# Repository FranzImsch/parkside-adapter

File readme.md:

## Overview

Lidl sells batteries for their Parkside-branded power tools. These are 5S lithium-ion batteries that are well-constructed and cost approximately €20 for the 4 Ah version. While the cells are not from premium brands, they appear to be of relatively high quality. For instance, the 4 Ah battery I purchased contains Sunpower INR19/66 cells. Detailed information about these cells can be found here:  
[Parkside INR18650E 2000mAh (Blue) Review](https://lygte-info.dk/review/batteries2012/Parkside%20INR18650E%202000mAh%20(Blue)%20UK.html)  
[Sunpower High-Rate Lithium-Ion Battery Specifications](https://www.sunpowernewenergy.com/product/18650-high-rate-lithium-ion-battery-20p/)

Currently, Lidl offers a USB charger add-on for these batteries, but it has significant limitations. Its output power is restricted to 15 W, and it does not support charging the battery via USB.  
[Product page](https://www.lidl.de/p/parkside-20-v-akku-ladeadapter-pwca-20-li-a1/p100363956)

The adaptor described here comprises a 3D-printed enclosure and a PCB with soldered contacts that connect to the battery terminals. The interface PCB includes two mounting locations for power modules.

The screenshot shows a cross section view of the assembly.

The bi-directional 100 W USB-C module, based on the IP2368 chip, is used in the current implementation.

Future developments are planned, including a 240 W power module and a PCB with a microcontroller and control logic.

## IP2368

The IP2368 chip is available in several firmware versions. I chose the IP2368_I2C_NACT variant, which supports I2C communication and can function as a USB-C source immediately upon connection to a battery, without requiring an initial connection to a charger. Sourcing this chip outside China is challenging; I obtained mine via [LCSC](https://www.lcsc.com/product-detail/Power-Management-Specialized_INJOINIC-IP2368_I2C_COUT_C5372184.html). Note that a quotation request is necessary, as this chip is typically not in stock.

## Tasks

- [ ] Create and expand documentation (better photos)
- [ ] Replace the overview photo  
- [ ] Design a PCB for the microcontroller  
- [ ] Test the 100 W power module

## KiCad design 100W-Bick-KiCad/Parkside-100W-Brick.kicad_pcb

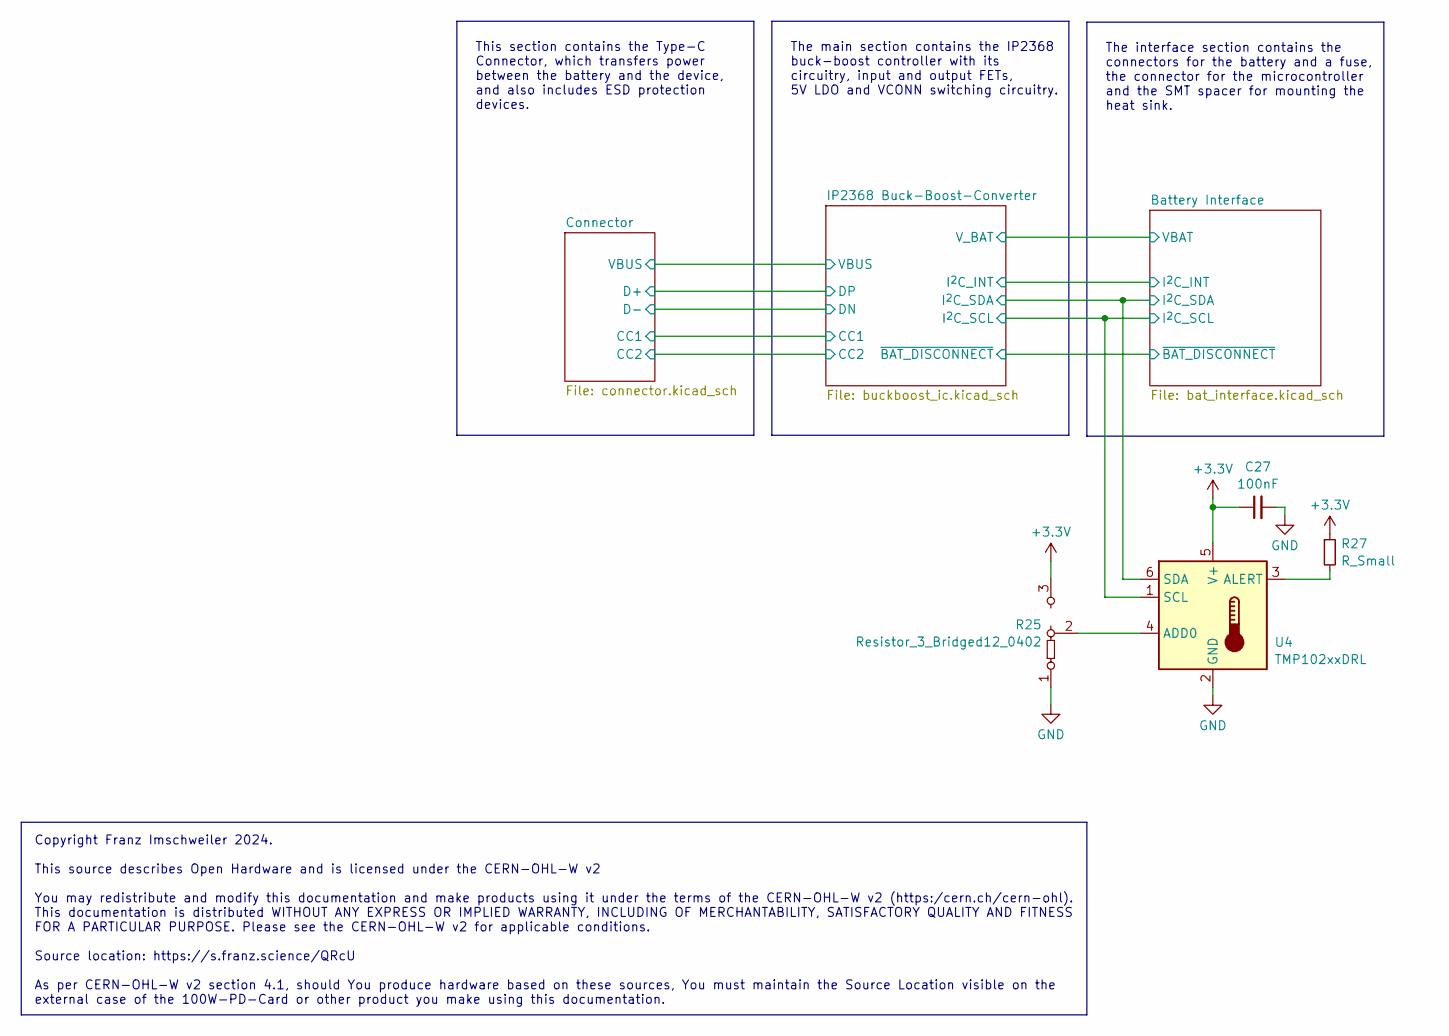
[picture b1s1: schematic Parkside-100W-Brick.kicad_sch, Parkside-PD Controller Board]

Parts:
C27: 100nF; C_0402_1005Metric_NoSilk
R25: Resistor_3_Bridged12_0402; R_0402_JUMPER3_NoSilk
R27: R_Small; R_0402_1005Metric_NoSilk
U4: TMP102xxDRL; SOT-563_NoSilk

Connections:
+3.3V: C27.1, R25.3 (B), R27.1, U4.5 (V+); also elsewhere on the board
/Battery Interface/I^{2}C_SCL: U4.1 (SCL); also elsewhere on the board
/Battery Interface/I^{2}C_SDA: U4.6 (SDA); also elsewhere on the board
GND: C27.2, R25.1 (A), U4.2 (GND); also elsewhere on the board
unnamed: R25.2 (C), U4.4 (ADD0)
unnamed: R27.2, U4.3 (ALERT)

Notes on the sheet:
The interface section contains the connectors for the battery and a fuse, the connector for the microcontroller and the SMT spacer for mounting the heat sink.
Copyright Franz Imschweiler 2024. This source describes Open Hardware and is licensed under the CERN-OHL-W v2 You may redistribute and modify this documentation and make products using it under the terms of the CERN-OHL-W v2 (https:/cern.ch/cern-ohl). This documentation is distributed WITHOUT ANY E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
This section contains the Type-C Connector, which transfers power between the battery and the device, and also includes ESD protection devices.
The main section contains the IP2368 buck-boost controller with its circuitry, input and output FETs, 5V LDO and VCONN switching circuitry.

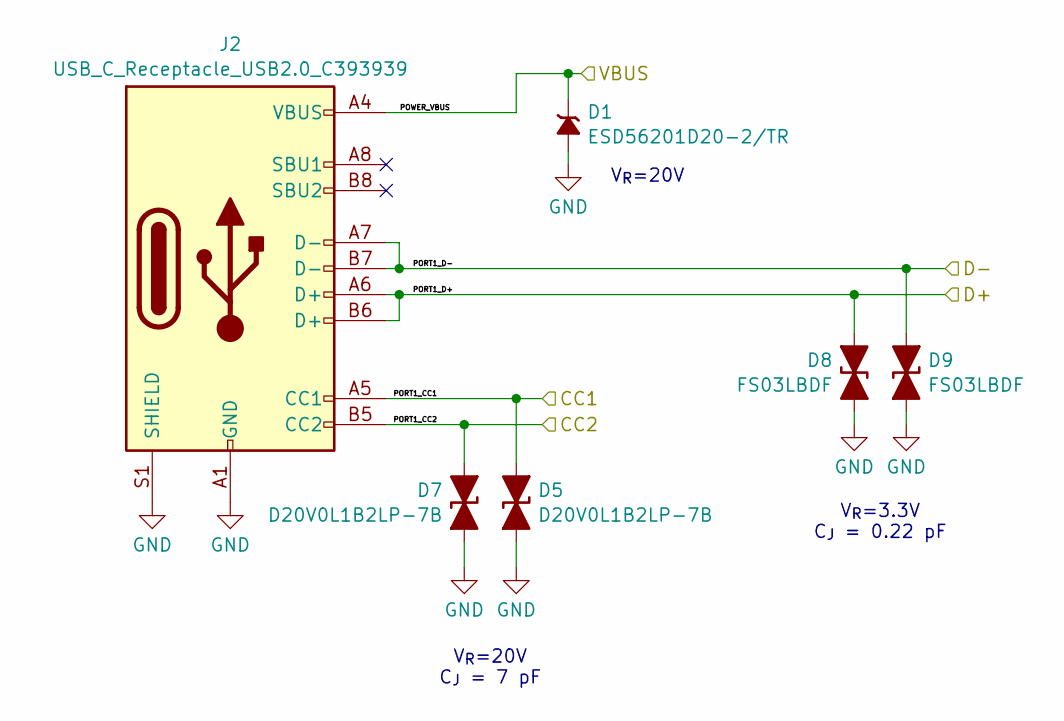
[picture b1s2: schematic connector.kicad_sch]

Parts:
D1: ESD56201D20-2/TR; ST_QFN1610_1_NoSilk
D5, D7: D20V0L1B2LP-7B; X1-DFN1006-2_P6X1_DIO
D8, D9: FS03LBDF; X1-DFN1006-2_P6X1_DIO
J2: USB_C_Receptacle_USB2.0_C393939; USB_C_Receptacle_C313131_TYPE-C-31-M-12

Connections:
/Connector/PORT1_CC1: D5.1 (A1), J2.A5 (CC1); also elsewhere on the board
/Connector/PORT1_CC2: D7.1 (A1), J2.B5 (CC2); also elsewhere on the board
/Connector/PORT1_D+: D8.1 (A1), J2.A6 (D+), J2.B6 (D+); also elsewhere on the board
/Connector/PORT1_D-: D9.1 (A1), J2.A7 (D-), J2.B7 (D-); also elsewhere on the board
/Connector/POWER_VBUS: D1.1 (K), J2.A4 (VBUS), J2.A9 (VBUS), J2.B4 (VBUS), J2.B9 (VBUS); also elsewhere on the board
GND: D1.2 (A), D5.2 (A2), D7.2 (A2), D8.2 (A2), D9.2 (A2), J2.A1 (GND), J2.A12 (GND), J2.B1 (GND), J2.B12 (GND), J2.S1 (SHIELD); also elsewhere on the board

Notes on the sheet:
V_{R}=20V C_{J} = 7 pF
V_{R}=20V
V_{R}=3.3V C_{J} = 0.22 pF

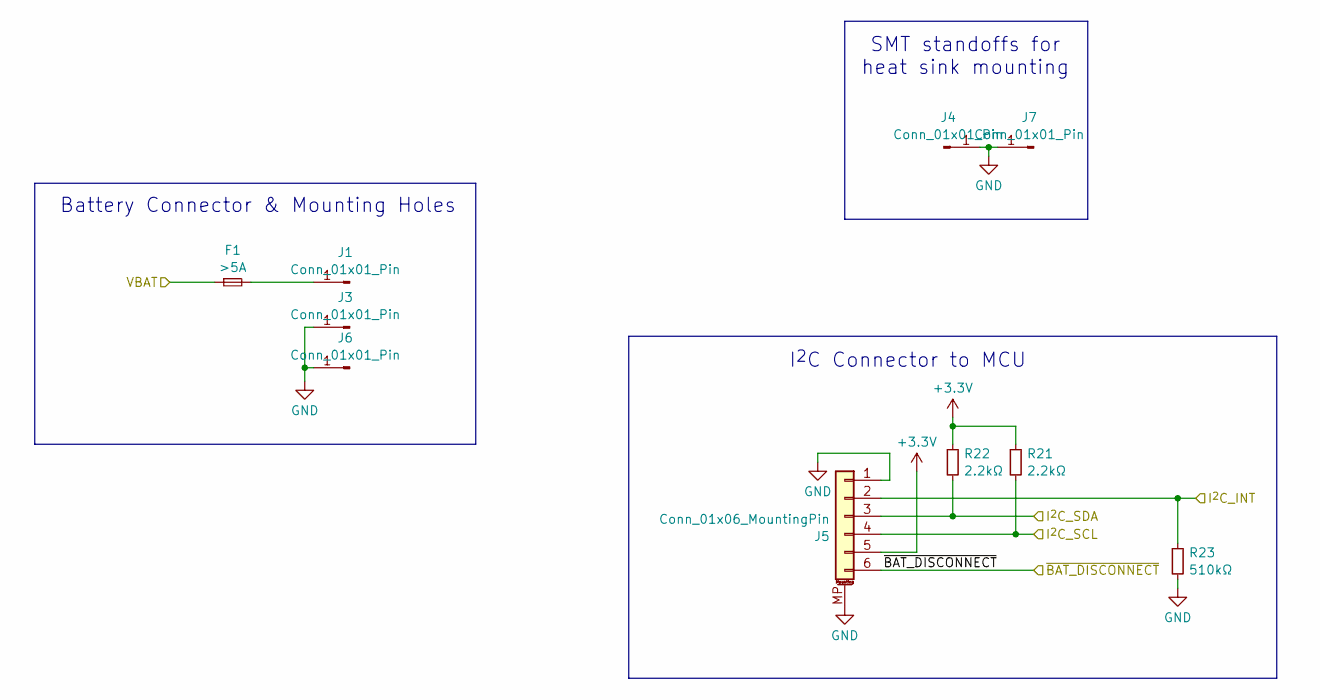
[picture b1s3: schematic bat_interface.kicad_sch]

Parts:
F1: >5A; Fuse_1206_3216Metric_NoSilk
J1, J3, J6: Conn_01x01_Pin; MountingHole_2.2mm_M2_Pad_Via_NoSilk
J4, J7: Conn_01x01_Pin; Mounting_Wuerth_WA-SMSI-M2_H6mm_9774060243
J5: Conn_01x06_MountingPin; JST_SH_SM06B-SRSS-TB_1x06-1MP_P1.00mm_Horizontal_NoSilk
R21, R22: 2.2kΩ; R_0402_1005Metric_NoSilk
R23: 510kΩ; R_0402_1005Metric_NoSilk

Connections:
+3.3V: J5.5, R21.1, R22.1; also elsewhere on the board
/Battery Interface/I^{2}C_INT: J5.2, R23.1; also elsewhere on the board
/Battery Interface/I^{2}C_SCL: J5.4, R21.2; also elsewhere on the board
/Battery Interface/I^{2}C_SDA: J5.3, R22.2; also elsewhere on the board
/Battery Interface/VBAT: F1.1; also elsewhere on the board
/Battery Interface/~BAT_DISCONNECT: J5.6; also elsewhere on the board
GND: J3.1, J4.1, J5.1, J5.MP (MountPin), J6.1, J7.1, R23.2; also elsewhere on the board
unnamed: F1.2, J1.1

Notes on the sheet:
Battery Connector & Mounting Holes
SMT standoffs for heat sink mounting
I^{2}C Connector to MCU

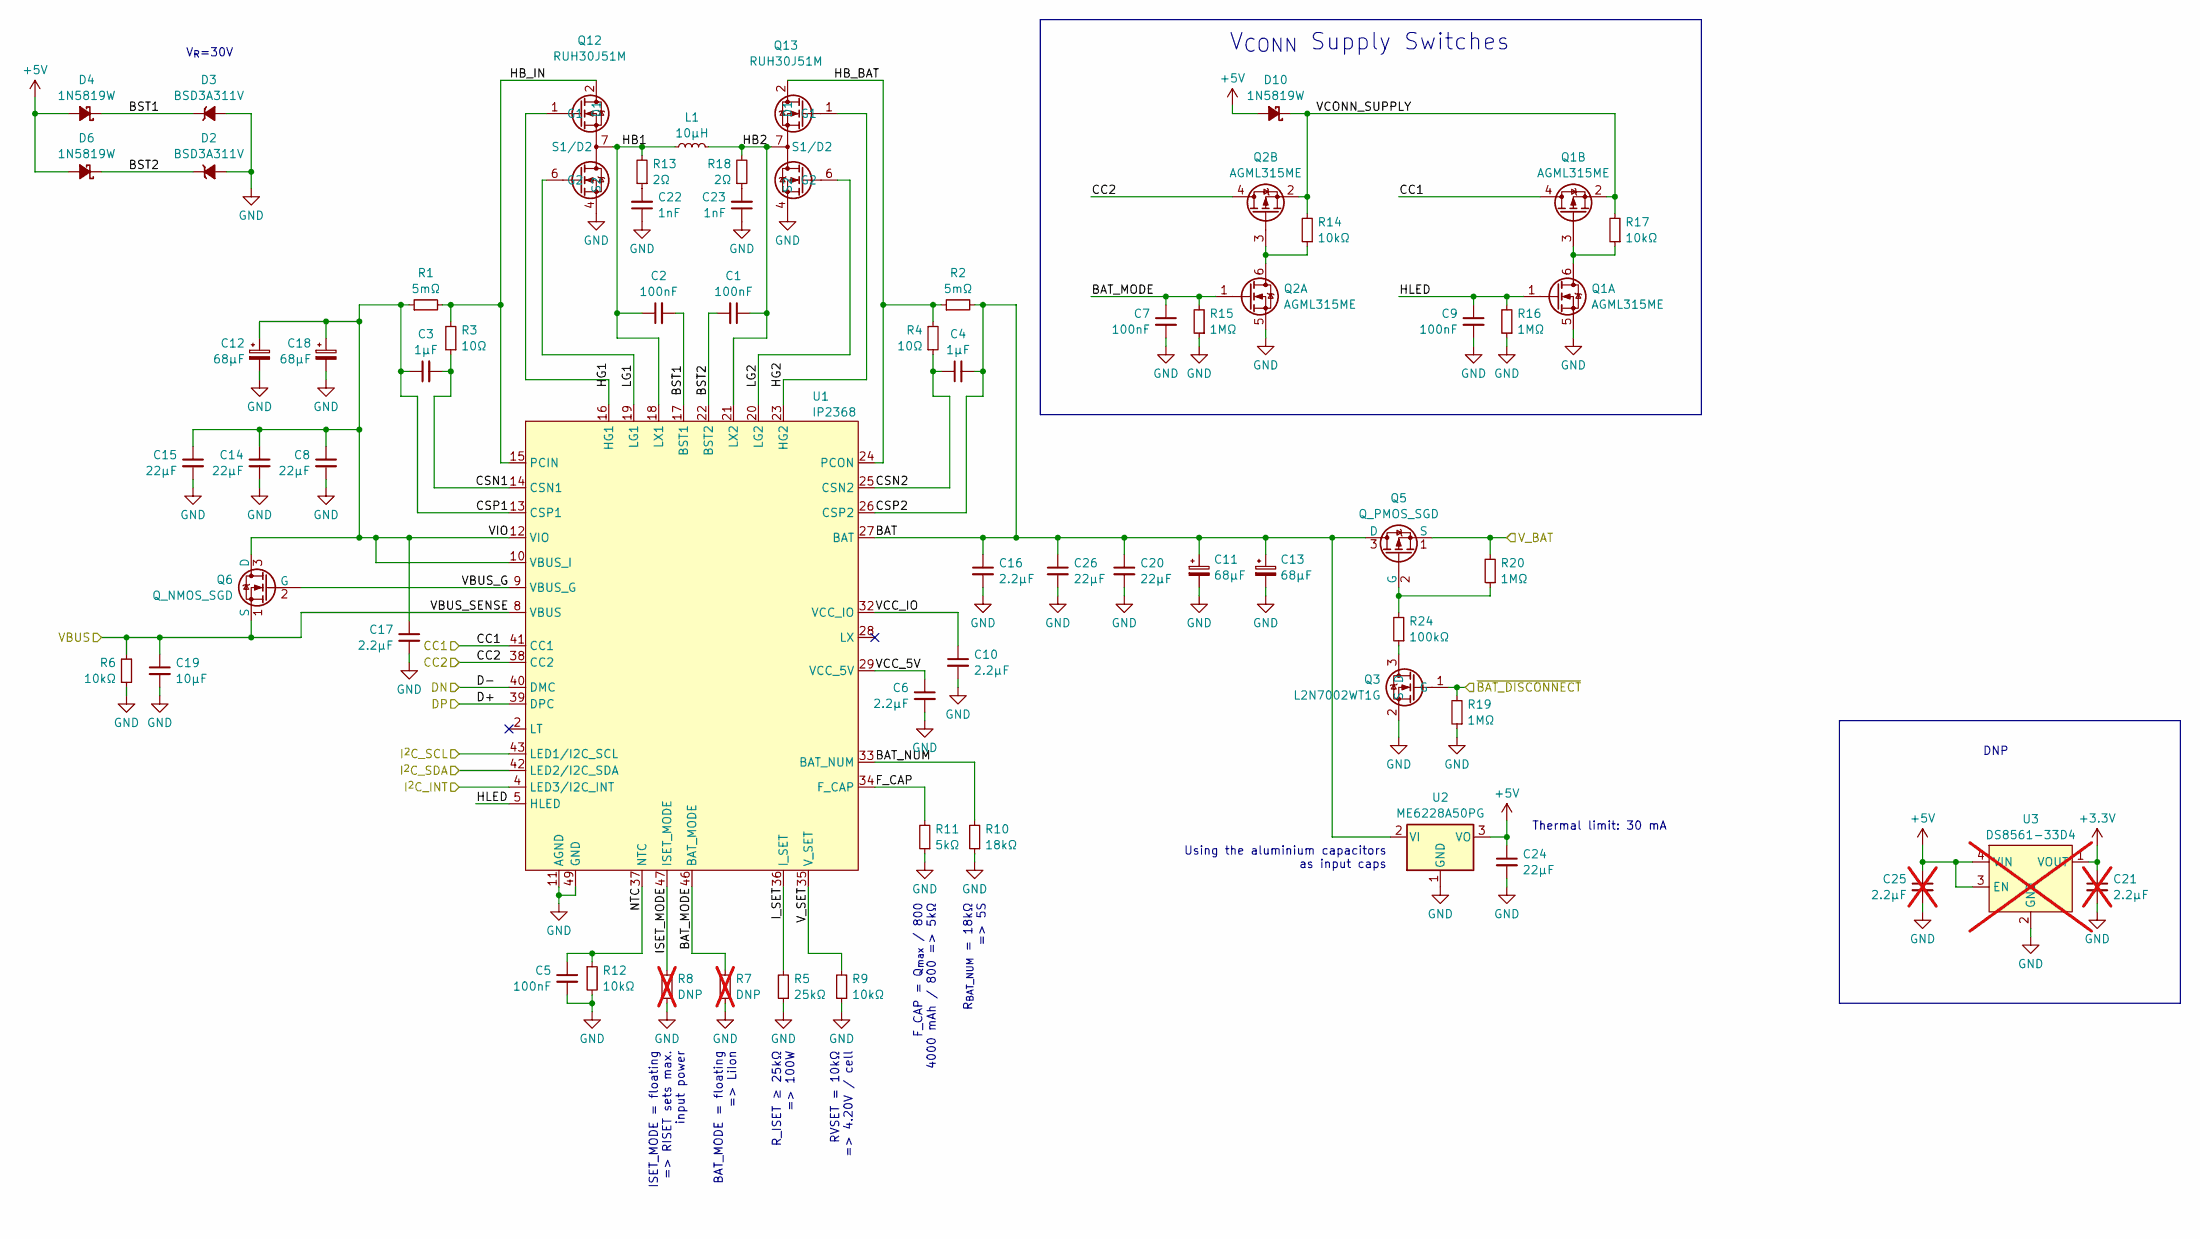
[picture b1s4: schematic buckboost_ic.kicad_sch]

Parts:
C1, C2, C5, C7, C9: 100nF; C_0402_1005Metric_NoSilk
C3, C4: 1µF; C_0402_1005Metric_NoSilk
C6, C10: 2.2µF; C_0402_1005Metric_NoSilk
C8, C14, C15, C20, C26: 22µF; C_0805_2012Metric_NoSilk
C11, C12, C13, C18: 68µF; CP_Elec_6.3x6.0
C16, C17: 2.2µF; C_0603_1608Metric_NoSilk
C19: 10µF; C_0603_1608Metric_NoSilk
C21, C25: 2.2µF; C_0402_1005Metric_NoSilk_DNP; not fitted
C22, C23: 1nF; C_0402_1005Metric_NoSilk
C24: 22µF; C_0603_1608Metric_NoSilk
D2, D3: BSD3A311V; D_SOD-323_SmallSilk
D4, D6, D10: 1N5819W; D_SOD-323_SmallSilk
L1: 10µH; 7443762504100
Q1, Q2: AGML315ME; SOT-23-6_NoSilk
Q3: L2N7002WT1G; SOT-323_SC-70_NoSilk
Q5: Q_PMOS_SGD; WDFN8_NoSilk
Q6: Q_NMOS_SGD; WDFN8_NoSilk
Q12, Q13: RUH30J51M; DFN-8_L6.0-W5.0-P1.27_AON6938
R1, R2: 5mΩ; R_1206_3216Metric_NoSilk
R3, R4: 10Ω; R_0402_1005Metric_NoSilk
R5: 25kΩ; R_0402_1005Metric_NoSilk
R6, R9, R12, R14, R17: 10kΩ; R_0402_1005Metric_NoSilk
R7, R8: DNP; R_0402_1005Metric_NoSilk_DNP; not fitted
R10: 18kΩ; R_0402_1005Metric_NoSilk
R11: 5kΩ; R_0402_1005Metric_NoSilk
R13, R18: 2Ω; R_0402_1005Metric_NoSilk
R15, R16, R19, R20: 1MΩ; R_0402_1005Metric_NoSilk
R24: 100kΩ; R_0402_1005Metric_NoSilk
U1: IP2368; QFN-48-1EP_7x7mm_P0.5mm_EP5.45x5.45mm_NoSilk
U2: ME6228A50PG; SOT-89-3_NoSilk
U3: DS8561-33D4; UDFN-4-1EP_1x1mm_P0.65mm_EP0.48x0.48mm_NoSilk_DNP; not fitted

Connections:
+3.3V: C21.1, U3.1 (VOUT); also elsewhere on the board
+5V: C24.1, C25.1, D4.2 (A), D6.2 (A), D10.2 (A), U2.3 (VO), U3.3 (EN), U3.4 (VIN)
/Battery Interface/I^{2}C_INT: U1.4 (LED3/I2C_INT); also elsewhere on the board
/Battery Interface/I^{2}C_SCL: U1.43 (LED1/I2C_SCL); also elsewhere on the board
/Battery Interface/I^{2}C_SDA: U1.42 (LED2/I2C_SDA); also elsewhere on the board
/Battery Interface/VBAT: Q5.1 (S), R20.2; also elsewhere on the board
/Battery Interface/~BAT_DISCONNECT: Q3.1 (G), R19.2; also elsewhere on the board
/Connector/PORT1_CC1: Q1.4 (DP), U1.41 (CC1); also elsewhere on the board
/Connector/PORT1_CC2: Q2.4 (DP), U1.38 (CC2); also elsewhere on the board
/Connector/PORT1_D+: U1.39 (DPC); also elsewhere on the board
/Connector/PORT1_D-: U1.40 (DMC); also elsewhere on the board
/Connector/POWER_VBUS: C19.1, Q6.1 (S), R6.2, U1.8 (VBUS); also elsewhere on the board
/IP2368 Buck-Boost-Converter/BAT: C4.2, C11.1, C13.1, C16.1, C20.1, C26.1, Q5.3 (D), R2.2, U1.26 (CSP2), U1.27 (BAT), U2.2 (VI)
/IP2368 Buck-Boost-Converter/BAT_MODE: C7.1, Q2.1 (GN), R7.2, R15.2, U1.46 (BAT_MODE)
/IP2368 Buck-Boost-Converter/BAT_NUM: R10.2, U1.33 (BAT_NUM)
/IP2368 Buck-Boost-Converter/BST1: C2.2, D3.1 (K), D4.1 (K), U1.17 (BST1)
/IP2368 Buck-Boost-Converter/BST2: C1.2, D2.1 (K), D6.1 (K), U1.22 (BST2)
/IP2368 Buck-Boost-Converter/CSN1: C3.2, R3.1, U1.14 (CSN1)
/IP2368 Buck-Boost-Converter/CSN2: C4.1, R4.1, U1.25 (CSN2)
/IP2368 Buck-Boost-Converter/CSP1: C3.1, C8.1, C12.1, C14.1, C15.1, C17.1, C18.1, Q6.3 (D), R1.1, U1.10 (VBUS_I), U1.12 (VIO), U1.13 (CSP1)
/IP2368 Buck-Boost-Converter/F_CAP: R11.2, U1.34 (F_CAP)
/IP2368 Buck-Boost-Converter/HB1: C2.1, L1.2, Q12.7 (S1/D2), R13.2, U1.18 (LX1)
/IP2368 Buck-Boost-Converter/HB2: C1.1, L1.1, Q13.7 (S1/D2), R18.2, U1.21 (LX2)
/IP2368 Buck-Boost-Converter/HB_BAT: Q13.2 (D1), R2.1, R4.2, U1.24 (PCON)
/IP2368 Buck-Boost-Converter/HB_IN: Q12.2 (D1), R1.2, R3.2, U1.15 (PCIN)
/IP2368 Buck-Boost-Converter/HG1: Q12.1 (G1), U1.16 (HG1)
/IP2368 Buck-Boost-Converter/HG2: Q13.1 (G1), U1.23 (HG2)
/IP2368 Buck-Boost-Converter/HLED: C9.1, Q1.1 (GN), R16.2, U1.5 (HLED)
/IP2368 Buck-Boost-Converter/ISET_MODE: R8.2, U1.47 (ISET_MODE)
/IP2368 Buck-Boost-Converter/I_SET: R5.2, U1.36 (I_SET)
/IP2368 Buck-Boost-Converter/LG1: Q12.6 (G2), U1.19 (LG1)
/IP2368 Buck-Boost-Converter/LG2: Q13.6 (G2), U1.20 (LG2)
/IP2368 Buck-Boost-Converter/NTC: C5.1, R12.1, U1.37 (NTC)
/IP2368 Buck-Boost-Converter/VBUS_G: Q6.2 (G), U1.9 (VBUS_G)
/IP2368 Buck-Boost-Converter/VCC_5V: C6.1, U1.29 (VCC_5V)
/IP2368 Buck-Boost-Converter/VCC_IO: C10.1, U1.32 (VCC_IO)
/IP2368 Buck-Boost-Converter/VCONN_SUPPLY: D10.1 (K), Q1.2 (SP), Q2.2 (SP), R14.2, R17.2
/IP2368 Buck-Boost-Converter/V_SET: R9.2, U1.35 (V_SET)
GND: C5.2, C6.2, C7.2, C8.2, C9.2, C10.2, C11.2, C12.2, C13.2, C14.2, C15.2, C16.2, C17.2, C18.2, C19.2, C20.2, C21.2, C22.1, C23.1, C24.2, C25.2, C26.2, D2.2 (A), D3.2 (A), Q1.5 (SN), Q2.5 (SN), Q3.2 (S), Q12.3 (S2), Q12.4 (S2), Q12.5 (S2), Q13.3 (S2), Q13.4 (S2), Q13.5 (S2), R5.1, R6.1, R7.1, R8.1, R9.1, R10.1, R11.1, R12.2, R15.1, R16.1, R19.1, U1.11 (AGND), U1.30 (AGND), U1.49 (GND), U2.1 (GND), U3.2 (GND), U3.5 (SGND); also elsewhere on the board
unnamed: C22.2, R13.1
unnamed: C23.2, R18.1
unnamed: Q1.3 (GP), Q1.6 (DN), R17.1
unnamed: Q2.3 (GP), Q2.6 (DN), R14.1
unnamed: Q3.3 (D), R24.1
unnamed: Q5.2 (G), R20.1, R24.2

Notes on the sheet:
F_CAP = Q_{max} / 800 4000 mAh / 800 => 5kΩ
BAT_MODE = floating => LiIon
RVSET = 10kΩ => 4.20V / cell
Thermal limit: 30 mA
Using the aluminium capacitors as input caps
ISET_MODE = floating => RISET sets max. input power
DNP
R_ISET ≥ 25kΩ => 100W
R_{BAT_NUM} = 18kΩ => 5S
V_{CONN} Supply Switches
V_{R}=30V

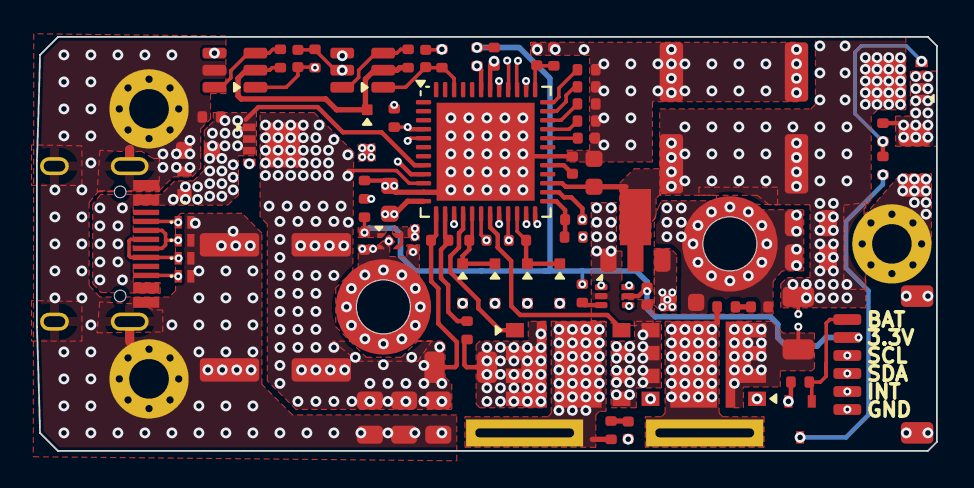
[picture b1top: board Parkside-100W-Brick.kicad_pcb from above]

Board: 8 copper layers, 50.0 x 23.0 mm, 81 parts (1 on the bottom side), 47 nets.

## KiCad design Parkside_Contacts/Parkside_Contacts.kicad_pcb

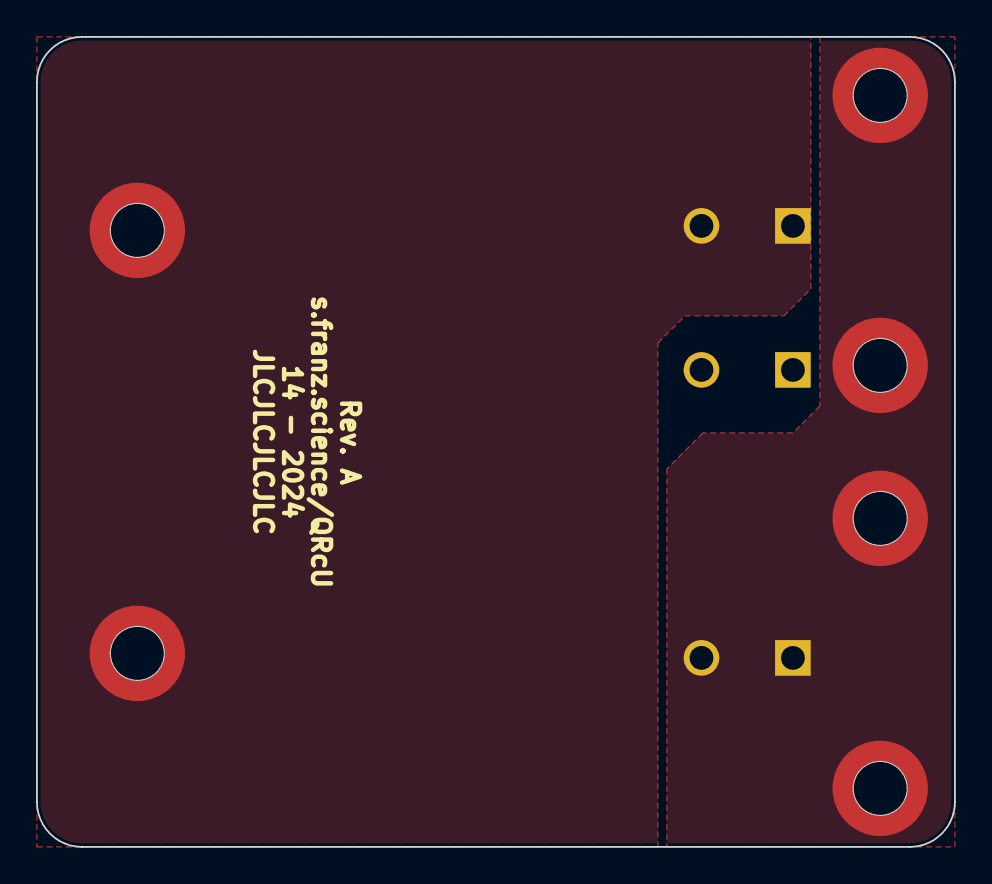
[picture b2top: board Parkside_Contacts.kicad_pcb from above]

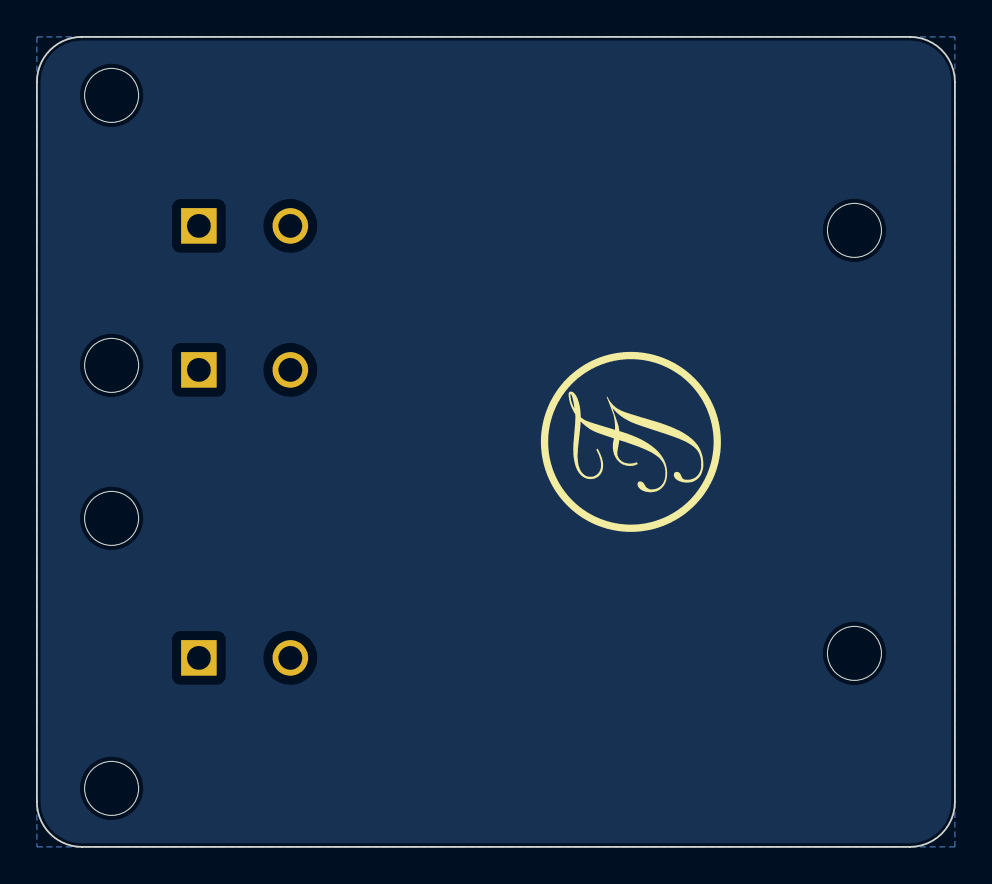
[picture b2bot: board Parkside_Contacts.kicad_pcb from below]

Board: 2 copper layers, 51.0 x 45.0 mm, 9 parts (3 on the bottom side), 2 nets, no tracks yet.

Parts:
J1, J2, J3: Conn_01x01_Pin; Keystone_4907
J5, J6, J7, J8, J9, J10: Conn_01x01; Mounting_Wuerth_WA-SMSI-M2_H6mm_9774060243

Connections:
GND: J3.1, J6.1, J8.1, J9.1, J10.1
unnamed: J1.1, J5.1, J7.1

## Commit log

2025-01-15 initialised repo
2025-01-15 removed image

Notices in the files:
100W-Bick-KiCad/Parkside-100W-Brick.kicad_sch:
As per CERN-OHL-W v2 section 4.1, should You produce hardware based on these sources, You must maintain the Source Location visible on the
external case of the 100W-PD-Card or other product you make using this documentation.
